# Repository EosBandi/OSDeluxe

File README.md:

# OSDeluxe

OSDeluxe is a color OSD with four video input, Picture in Picture function for Mavlink flight controllers. It using a Renesas TW2837 Video Mux ASIC
and a Teensy 3.2.

# History

This project, just like many others has a long history. It started as blue screen eliminator, for FPV flights. Before custom made FPV monitors, it was a constant problem that normal monitors went dark or blue when video signal become noisy. A cheap video quad switch based on a TW2823 (earlier version of the chip currently used) was reprogrammed to digitize incoming video in a free running mode, and since it already had four inputs and PIP capabilities it was also added to the mix. (The idea come from a Russian webpage http://we.easyelectronics.ru/howwork/kvadrator-izobrazheniya-dlya-sistem-videonablyudeniya.html and confidential datasheet of TW2823 was found on Chinese page.) 
The TW2823 chip has color OSD capabilities and it seemed a good idea to make a PIP OSD for FPV use with it. After experimenting for a while it turned out that the speed of OSD functions are too slow to use  for FPV, so the project was stalled. Then a new version of the chip come out, the TW2837 with accelerated OSD functions. Using these functions with some tuned code, now it is possible to have a decent color OSD with around 10Hz refresh rate.

# TW2837
The TW2837 is a four channel video and audio controller designed for security applications by Renesas (Originally TechWell, then Intersil). It has four PAL/NTSC video decoders (digitizers) and dual video encoders. Video encoders has scalers and video enhancer built in. Decoders and encoders are connected to a MUX engine which provides two display paths and an accelerated graphic overlay (OSD) for each paths. Unlike older TW28xx chips, datasheet for TW2837 is freely available.  (unfortunately OSD sections of the datasheet are quite rudimentary, so it needed a lots of experimenting to make it work.)
Communication with the chip can be done via I2C interface (up to 10Mhz!! clock speed) or via a parallel interface.

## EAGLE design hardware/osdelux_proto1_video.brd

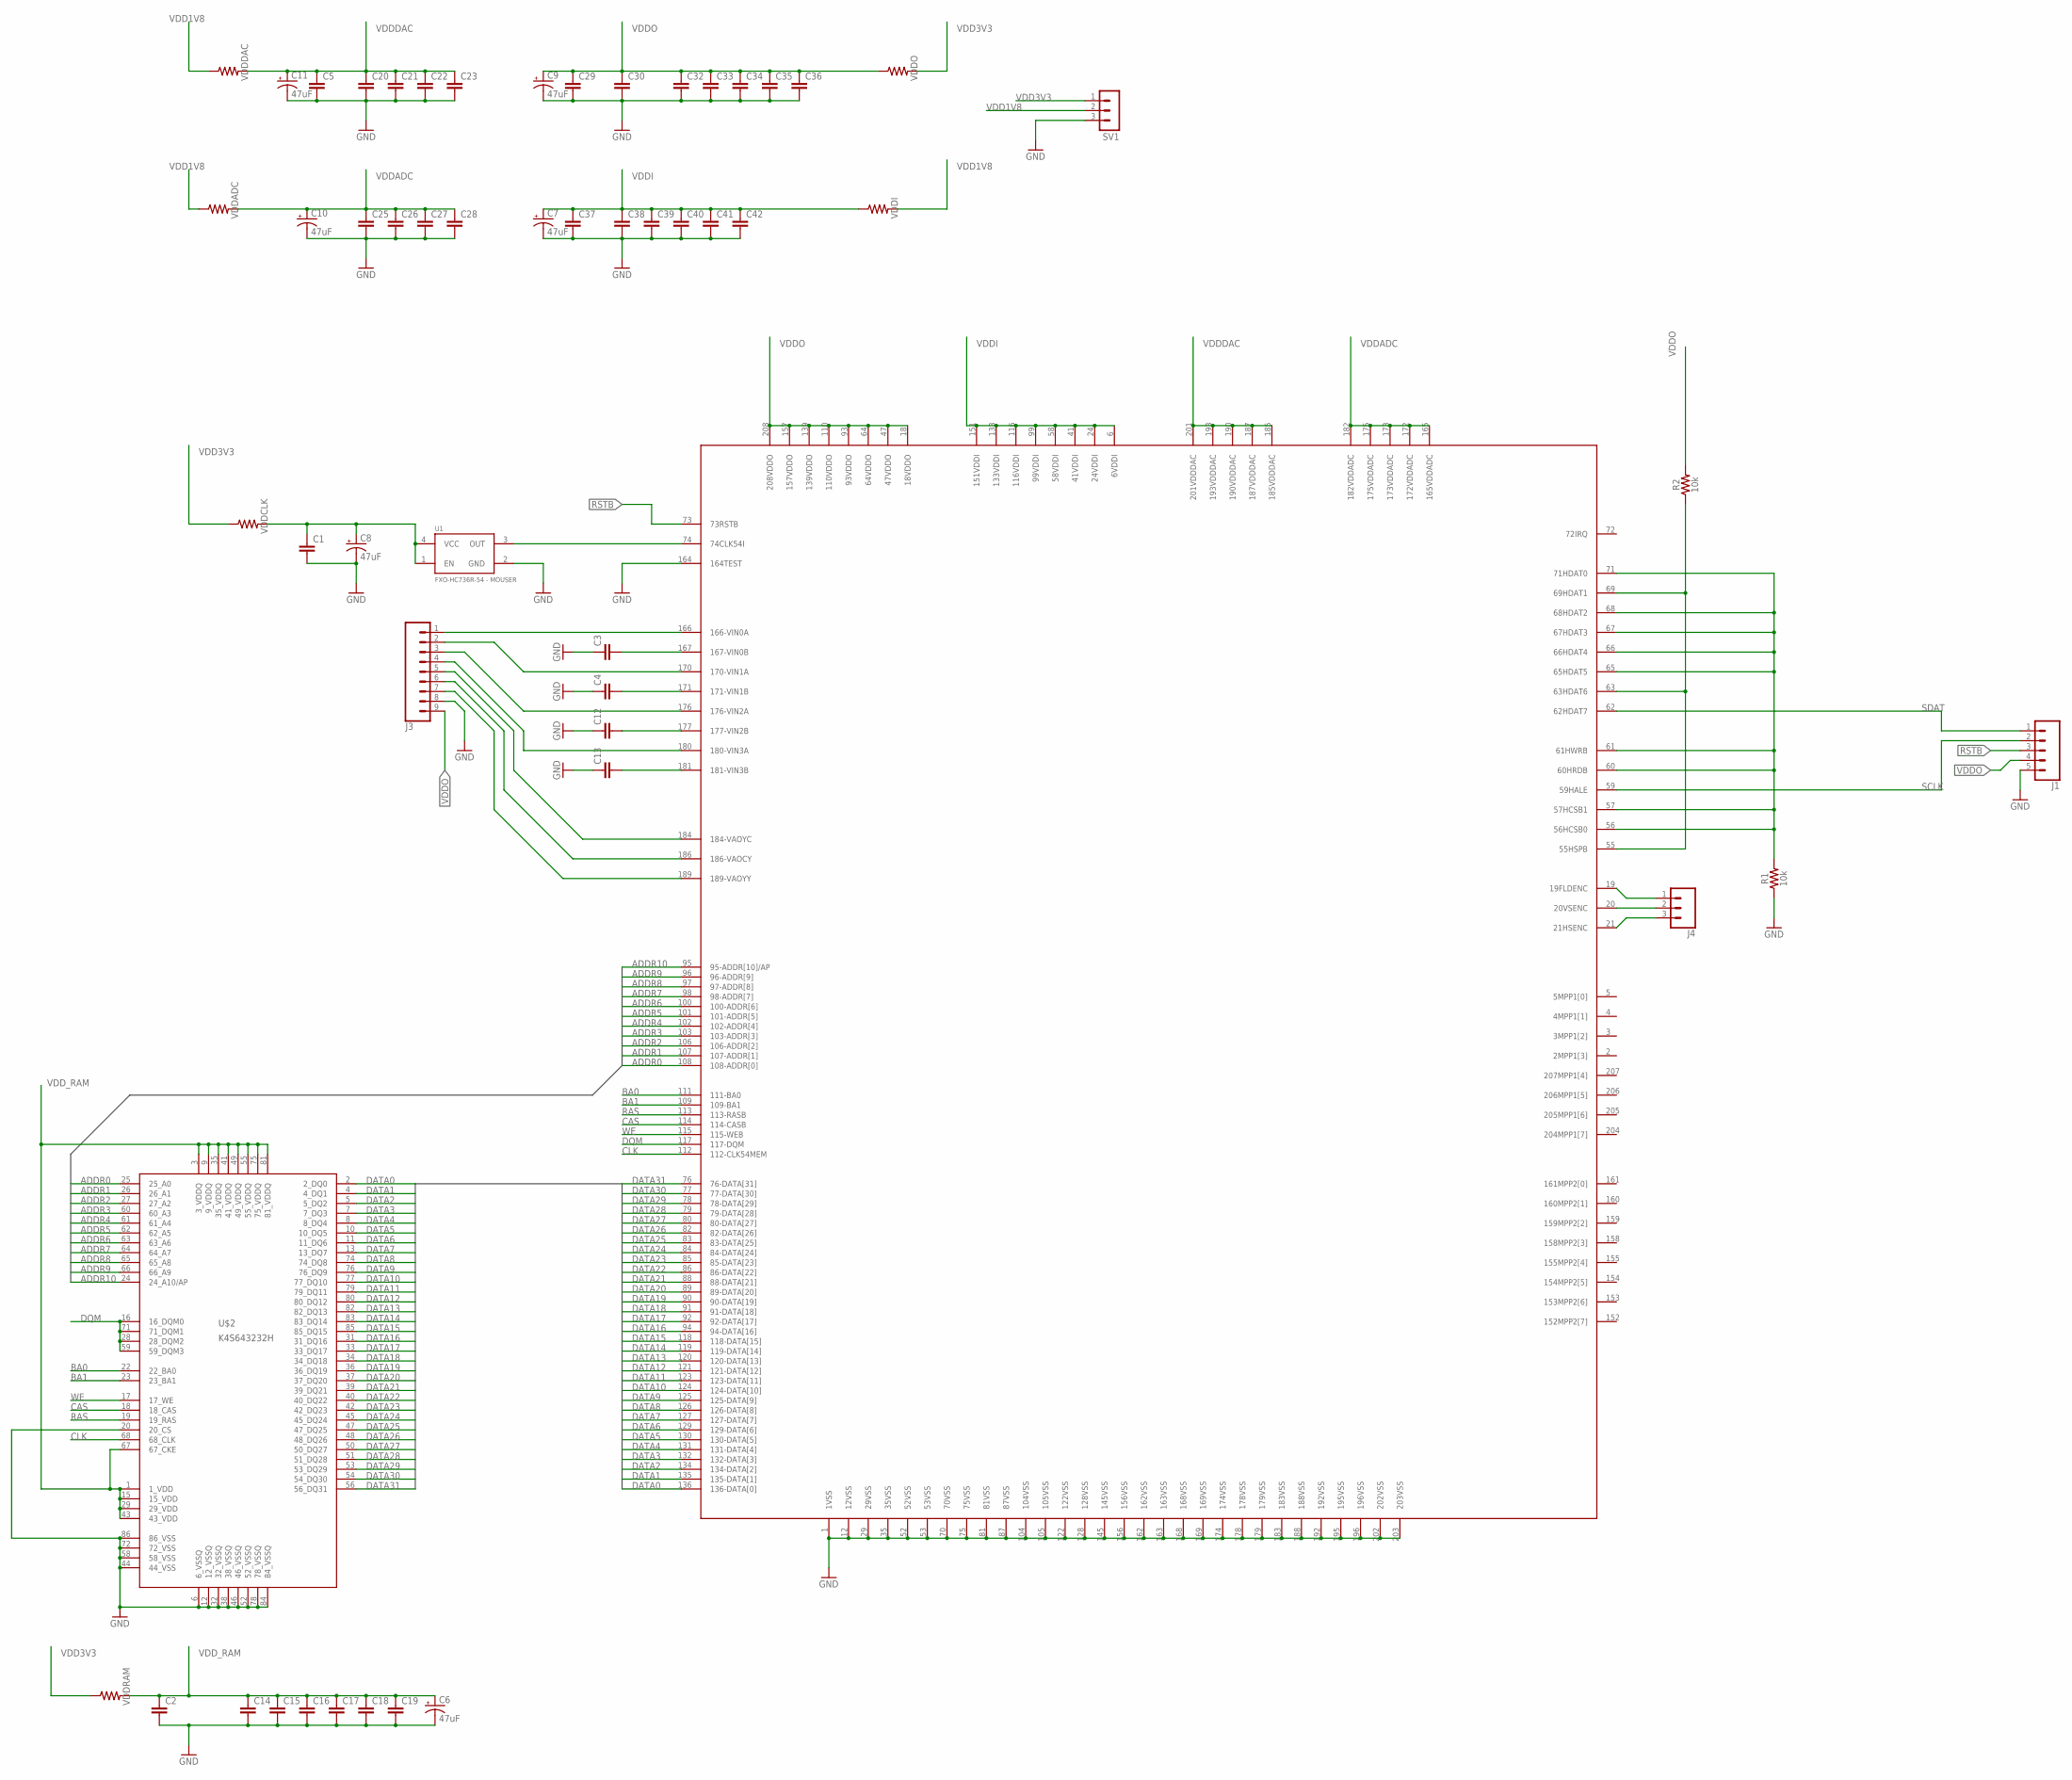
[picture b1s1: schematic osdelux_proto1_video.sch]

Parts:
C1, C2, C3, C4, C5, C12, C13, C14, C15, C16, C17, C18, C19, C20, C21, C22, C23, C25, C26, C27, C28, C29, C30, C32, C33, C34, C35, C36, C37, C38, C39, C40, C41, C42: CAP0805; 0805
C6, C7, C8, C9, C10, C11: 47uF; EIA3528
J1: CONN_05LOCK_LONGPADS; 1X05_LOCK_LONGPADS
J3: CONN_09LOCK-LONGPADS; 1X09_LOCK_LONGPADS
J4: CONN_03LOCK_LONGPADS; 1X03_LOCK_LONGPADS
R1, R2: 10k; 0805
SV1: MA03-1
U1: FXO-HC736R-54 - MOUSER; CRYSTAL-SMD-7.5X5.2-6PIN
U$1: TW2823; LQFP208
U$2: K4S643232H; TSOP86
VDDADC: 1206
VDDCLK: 1206
VDDDAC: 1206
VDDI: 1206
VDDO: 1206
VDDRAM: 1206

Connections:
72IRQ: U$1.72 (72IRQ)
ADDR0: U$1.108 (108-ADDR[0]), U$2.25 (25_A0)
ADDR1: U$1.107 (107-ADDR[1]), U$2.26 (26_A1)
ADDR2: U$1.106 (106-ADDR[2]), U$2.27 (27_A2)
ADDR3: U$1.103 (103-ADDR[3]), U$2.60 (60_A3)
ADDR4: U$1.102 (102-ADDR[4]), U$2.61 (61_A4)
ADDR5: U$1.101 (101-ADDR[5]), U$2.62 (62_A5)
ADDR6: U$1.100 (100-ADDR[6]), U$2.63 (63_A6)
ADDR7: U$1.98 (98-ADDR[7]), U$2.64 (64_A7)
ADDR8: U$1.97 (97-ADDR[8]), U$2.65 (65_A8)
ADDR9: U$1.96 (96-ADDR[9]), U$2.66 (66_A9)
ADDR10: U$1.95 (95-ADDR[10]/AP), U$2.24 (24_A10/AP)
BA0: U$1.111 (111-BA0), U$2.22 (22_BA0)
BA1: U$1.109 (109-BA1), U$2.23 (23_BA1)
CAS: U$1.114 (114-CASB), U$2.18 (18_CAS)
CLK: U$1.112 (112-CLK54MEM), U$2.68 (68_CLK)
DATA0: U$1.136 (136-DATA[0]), U$2.2 (2_DQ0)
DATA1: U$1.135 (135-DATA[1]), U$2.4 (4_DQ1)
DATA2: U$1.134 (134-DATA[2]), U$2.5 (5_DQ2)
DATA3: U$1.132 (132-DATA[3]), U$2.7 (7_DQ3)
DATA4: U$1.131 (131-DATA[4]), U$2.8 (8_DQ4)
DATA5: U$1.130 (130-DATA[5]), U$2.10 (10_DQ5)
DATA6: U$1.129 (129-DATA[6]), U$2.11 (11_DQ6)
DATA7: U$1.127 (127-DATA[7]), U$2.13 (13_DQ7)
DATA8: U$1.126 (126-DATA[8]), U$2.74 (74_DQ8)
DATA9: U$1.125 (125-DATA[9]), U$2.76 (76_DQ9)
DATA10: U$1.124 (124-DATA[10]), U$2.77 (77_DQ10)
DATA11: U$1.123 (123-DATA[11]), U$2.79 (79_DQ11)
DATA12: U$1.121 (121-DATA[12]), U$2.80 (80_DQ12)
DATA13: U$1.120 (120-DATA[13]), U$2.82 (82_DQ13)
DATA14: U$1.119 (119-DATA[14]), U$2.83 (83_DQ14)
DATA15: U$1.118 (118-DATA[15]), U$2.85 (85_DQ15)
DATA16: U$1.94 (94-DATA[16]), U$2.31 (31_DQ16)
DATA17: U$1.92 (92-DATA[17]), U$2.33 (33_DQ17)
DATA18: U$1.91 (91-DATA[18]), U$2.34 (34_DQ18)
DATA19: U$1.90 (90-DATA[19]), U$2.36 (36_DQ19)
DATA20: U$1.89 (89-DATA[20]), U$2.37 (37_DQ20)
DATA21: U$1.88 (88-DATA[21]), U$2.39 (39_DQ21)
DATA22: U$1.86 (86-DATA[22]), U$2.40 (40_DQ22)
DATA23: U$1.85 (85-DATA[23]), U$2.42 (42_DQ23)
DATA24: U$1.84 (84-DATA[24]), U$2.45 (45_DQ24)
DATA25: U$1.83 (83-DATA[25]), U$2.47 (47_DQ25)
DATA26: U$1.82 (82-DATA[26]), U$2.48 (48_DQ26)
DATA27: U$1.80 (80-DATA[27]), U$2.50 (50_DQ27)
DATA28: U$1.79 (79-DATA[28]), U$2.51 (51_DQ28)
DATA29: U$1.78 (78-DATA[29]), U$2.53 (53_DQ29)
DATA30: U$1.77 (77-DATA[30]), U$2.54 (54_DQ30)
DATA31: U$1.76 (76-DATA[31]), U$2.56 (56_DQ31)
DQM: U$1.117 (117-DQM), U$2.16 (16_DQM0), U$2.28 (28_DQM2), U$2.59 (59_DQM3), U$2.71 (71_DQM1)
FLD: J4.1, U$1.19 (19FLDENC)
GND: C1.2, C2.2, C3.1, C4.1, C5.2, C6.C (-), C7.C (-), C8.C (-), C9.C (-), C10.C (-), C11.C (-), C12.1, C13.1, C14.2, C15.2, C16.2, C17.2, C18.2, C19.2, C20.2, C21.2, C22.2, C23.2, C25.2, C26.2, C27.2, C28.2, C29.2, C30.2, C32.2, C33.2, C34.2, C35.2, C36.2, C37.2, C38.2, C39.2, C40.2, C41.2, C42.2, J1.5, J3.8, R1.1, SV1.3, U1.2 (GND), U$1.1 (1VSS), U$1.12 (12VSS), U$1.29 (29VSS), U$1.35 (35VSS), U$1.52 (52VSS), U$1.53 (53VSS), U$1.70 (70VSS), U$1.75 (75VSS), U$1.81 (81VSS), U$1.87 (87VSS), U$1.104 (104VSS), U$1.105 (105VSS), U$1.122 (122VSS), U$1.128 (128VSS), U$1.145 (145VSS), U$1.156 (156VSS), U$1.162 (162VSS), U$1.163 (163VSS), U$1.164 (164TEST), U$1.168 (168VSS), U$1.169 (169VSS), U$1.174 (174VSS), U$1.178 (178VSS), U$1.179 (179VSS), U$1.183 (183VSS), U$1.188 (188VSS), U$1.192 (192VSS), U$1.195 (195VSS), U$1.196 (196VSS), U$1.202 (202VSS), U$1.203 (203VSS), U$2.6 (6_VSSQ), U$2.12 (12_VSSQ), U$2.20 (20_CS), U$2.32 (32_VSSQ), U$2.38 (38_VSSQ), U$2.44 (44_VSS), U$2.46 (46_VSSQ), U$2.52 (52_VSSQ), U$2.58 (58_VSS), U$2.72 (72_VSS), U$2.78 (78_VSSQ), U$2.84 (84_VSSQ), U$2.86 (86_VSS)
HSYNC: J4.3, U$1.21 (21HSENC)
unnamed: C1.1, C8.A (+), U1.1 (EN), U1.4 (VCC), VDDCLK.2
unnamed: U1.3 (OUT), U$1.74 (74CLK54I)
unnamed: C3.2, U$1.167 (167-VIN0B)
unnamed: C4.2, U$1.171 (171-VIN1B)
unnamed: C12.2, U$1.177 (177-VIN2B)
unnamed: C13.2, U$1.181 (181-VIN3B)
unnamed: R1.2, U$1.56 (56HCSB0), U$1.57 (57HCSB1), U$1.60 (60HRDB), U$1.61 (61HWRB), U$1.65 (65HDAT5), U$1.66 (66HDAT4), U$1.67 (67HDAT3), U$1.68 (68HDAT2), U$1.71 (71HDAT0)
unnamed: R2.1, U$1.55 (55HSPB), U$1.63 (63HDAT6), U$1.69 (69HDAT1)
RAS: U$1.113 (113-RASB), U$2.19 (19_RAS)
RSTB: J1.3, U$1.73 (73RSTB)
SCLK: J1.2, U$1.59 (59HALE)
SDAT: J1.1, U$1.62 (62HDAT7)
VAOCY: J3.6, U$1.186 (186-VAOCY)
VAOYC: J3.5, U$1.184 (184-VAOYC)
VAOYY: J3.7, U$1.189 (189-VAOYY)
VDD1V8: SV1.2, VDDADC.1, VDDDAC.1, VDDI.2
VDD3V3: SV1.1, VDDCLK.1, VDDO.2, VDDRAM.1
VDDADC: C10.A (+), C25.1, C26.1, C27.1, C28.1, U$1.165 (165VDDADC), U$1.172 (172VDDADC), U$1.173 (173VDDADC), U$1.175 (175VDDADC), U$1.182 (182VDDADC), VDDADC.2
VDDDAC: C5.1, C11.A (+), C20.1, C21.1, C22.1, C23.1, U$1.185 (185VDDDAC), U$1.187 (187VDDDAC), U$1.190 (190VDDDAC), U$1.193 (193VDDDAC), U$1.201 (201VDDDAC), VDDDAC.2
VDDI: C7.A (+), C37.1, C38.1, C39.1, C40.1, C41.1, C42.1, U$1.6 (6VDDI), U$1.24 (24VDDI), U$1.41 (41VDDI), U$1.58 (58VDDI), U$1.99 (99VDDI), U$1.116 (116VDDI), U$1.133 (133VDDI), U$1.151 (151VDDI), VDDI.1
VDDO: C9.A (+), C29.1, C30.1, C32.1, C33.1, C34.1, C35.1, C36.1, J1.4, J3.9, R2.2, U$1.18 (18VDDO), U$1.47 (47VDDO), U$1.64 (64VDDO), U$1.93 (93VDDO), U$1.110 (110VDDO), U$1.139 (139VDDO), U$1.157 (157VDDO), U$1.208 (208VDDO), VDDO.1
VDD_RAM: C2.1, C6.A (+), C14.1, C15.1, C16.1, C17.1, C18.1, C19.1, U$2.1 (1_VDD), U$2.3 (3_VDDQ), U$2.9 (9_VDDQ), U$2.15 (15_VDD), U$2.29 (29_VDD), U$2.35 (35_VDDQ), U$2.41 (41_VDDQ), U$2.43 (43_VDD), U$2.49 (49_VDDQ), U$2.55 (55_VDDQ), U$2.67 (67_CKE), U$2.75 (75_VDDQ), U$2.81 (81_VDDQ), VDDRAM.2
VIN0: J3.1, U$1.166 (166-VIN0A)
VIN1: J3.2, U$1.170 (170-VIN1A)
VIN2: J3.3, U$1.176 (176-VIN2A)
VIN3: J3.4, U$1.180 (180-VIN3A)
VSYNC: J4.2, U$1.20 (20VSENC)
WE: U$1.115 (115-WEB), U$2.17 (17_WE)

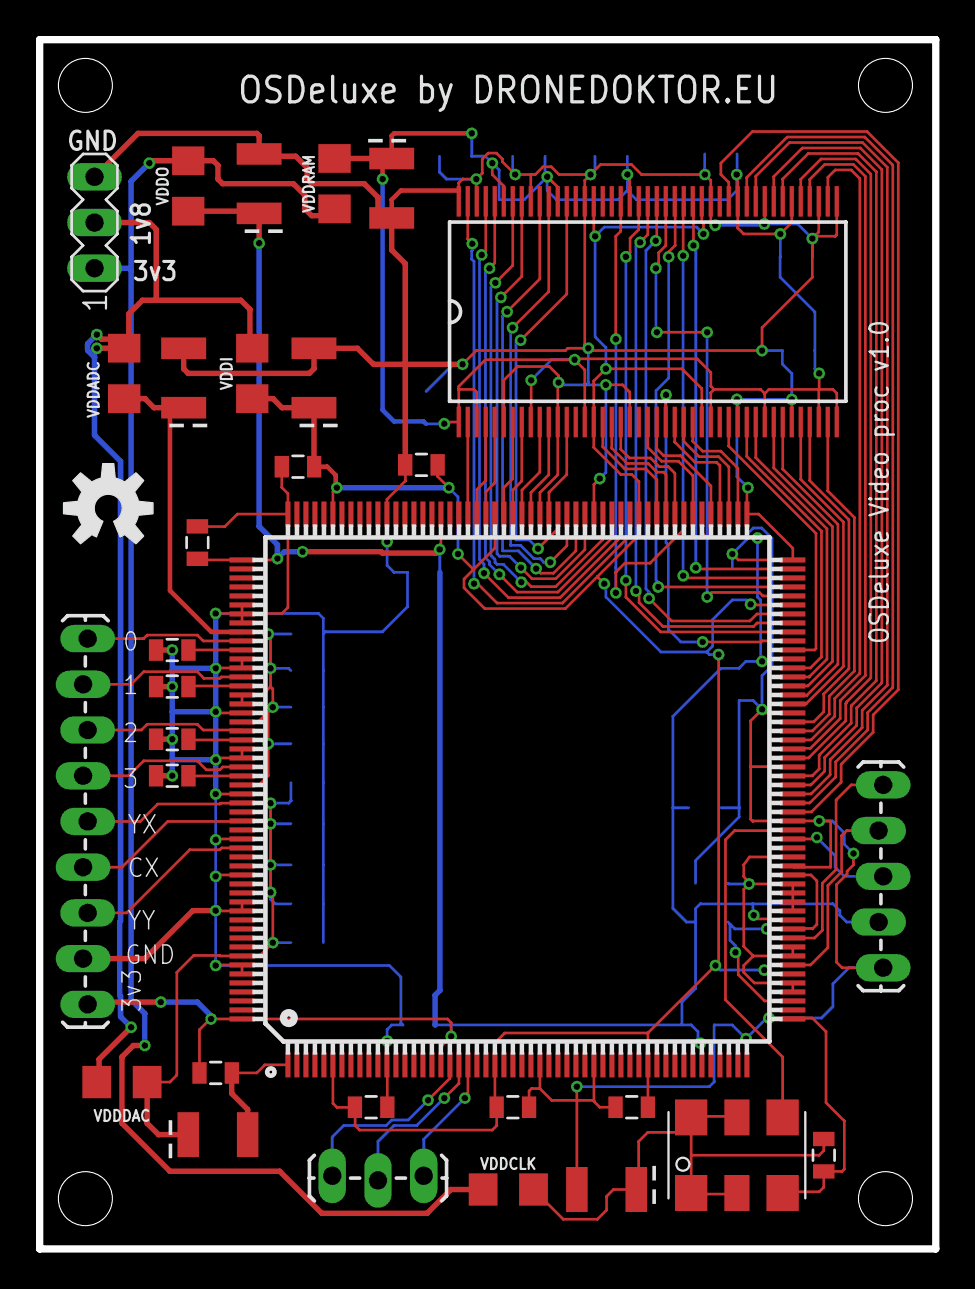
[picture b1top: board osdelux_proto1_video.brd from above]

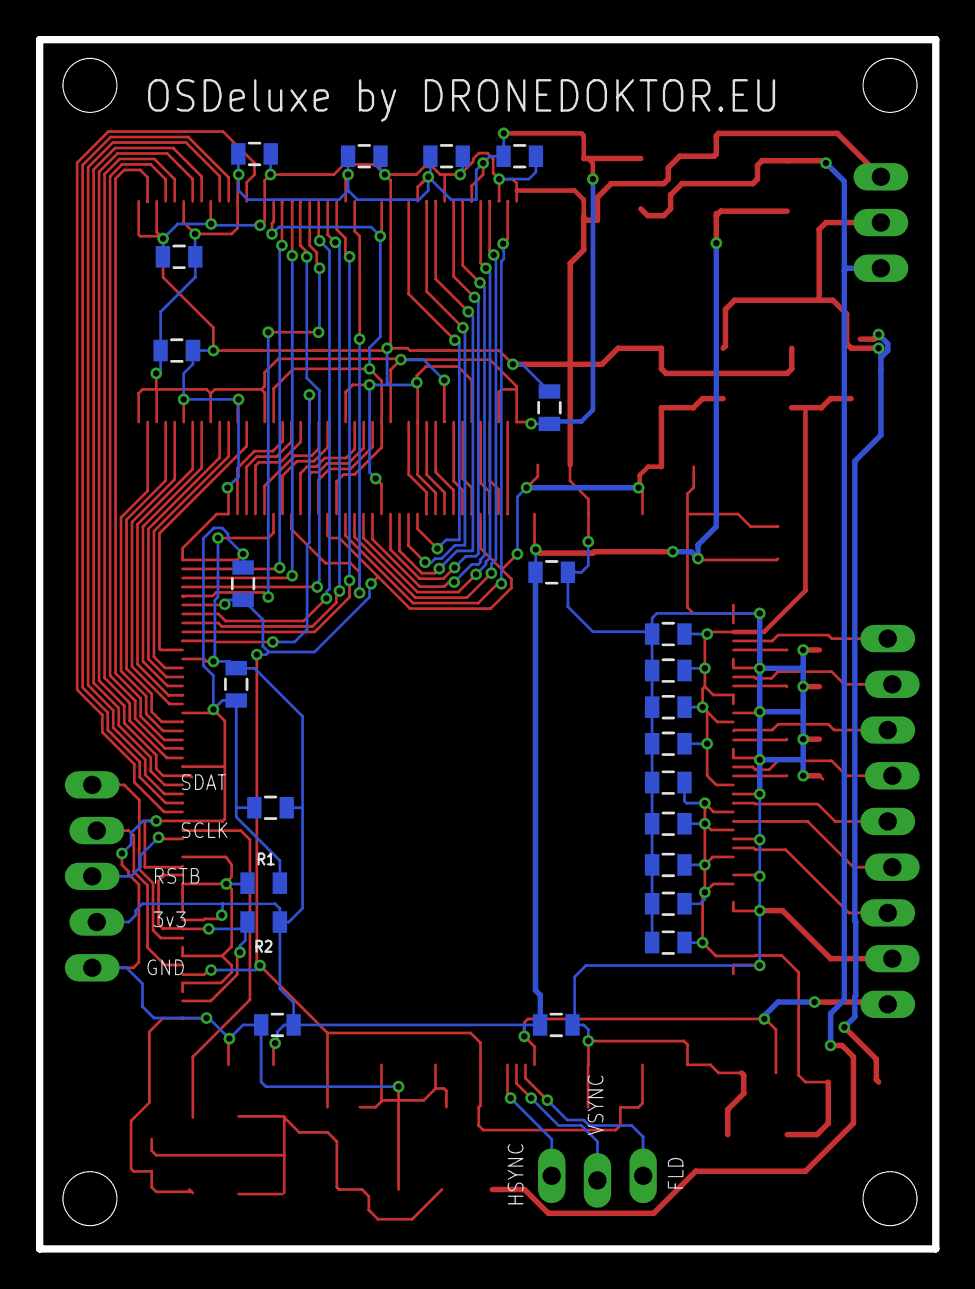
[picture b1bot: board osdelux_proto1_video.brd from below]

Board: 2 copper layers, 49.8 x 67.2 mm, 56 parts (24 on the bottom side), 79 nets.

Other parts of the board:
U$3: OSHW-LOGO-M

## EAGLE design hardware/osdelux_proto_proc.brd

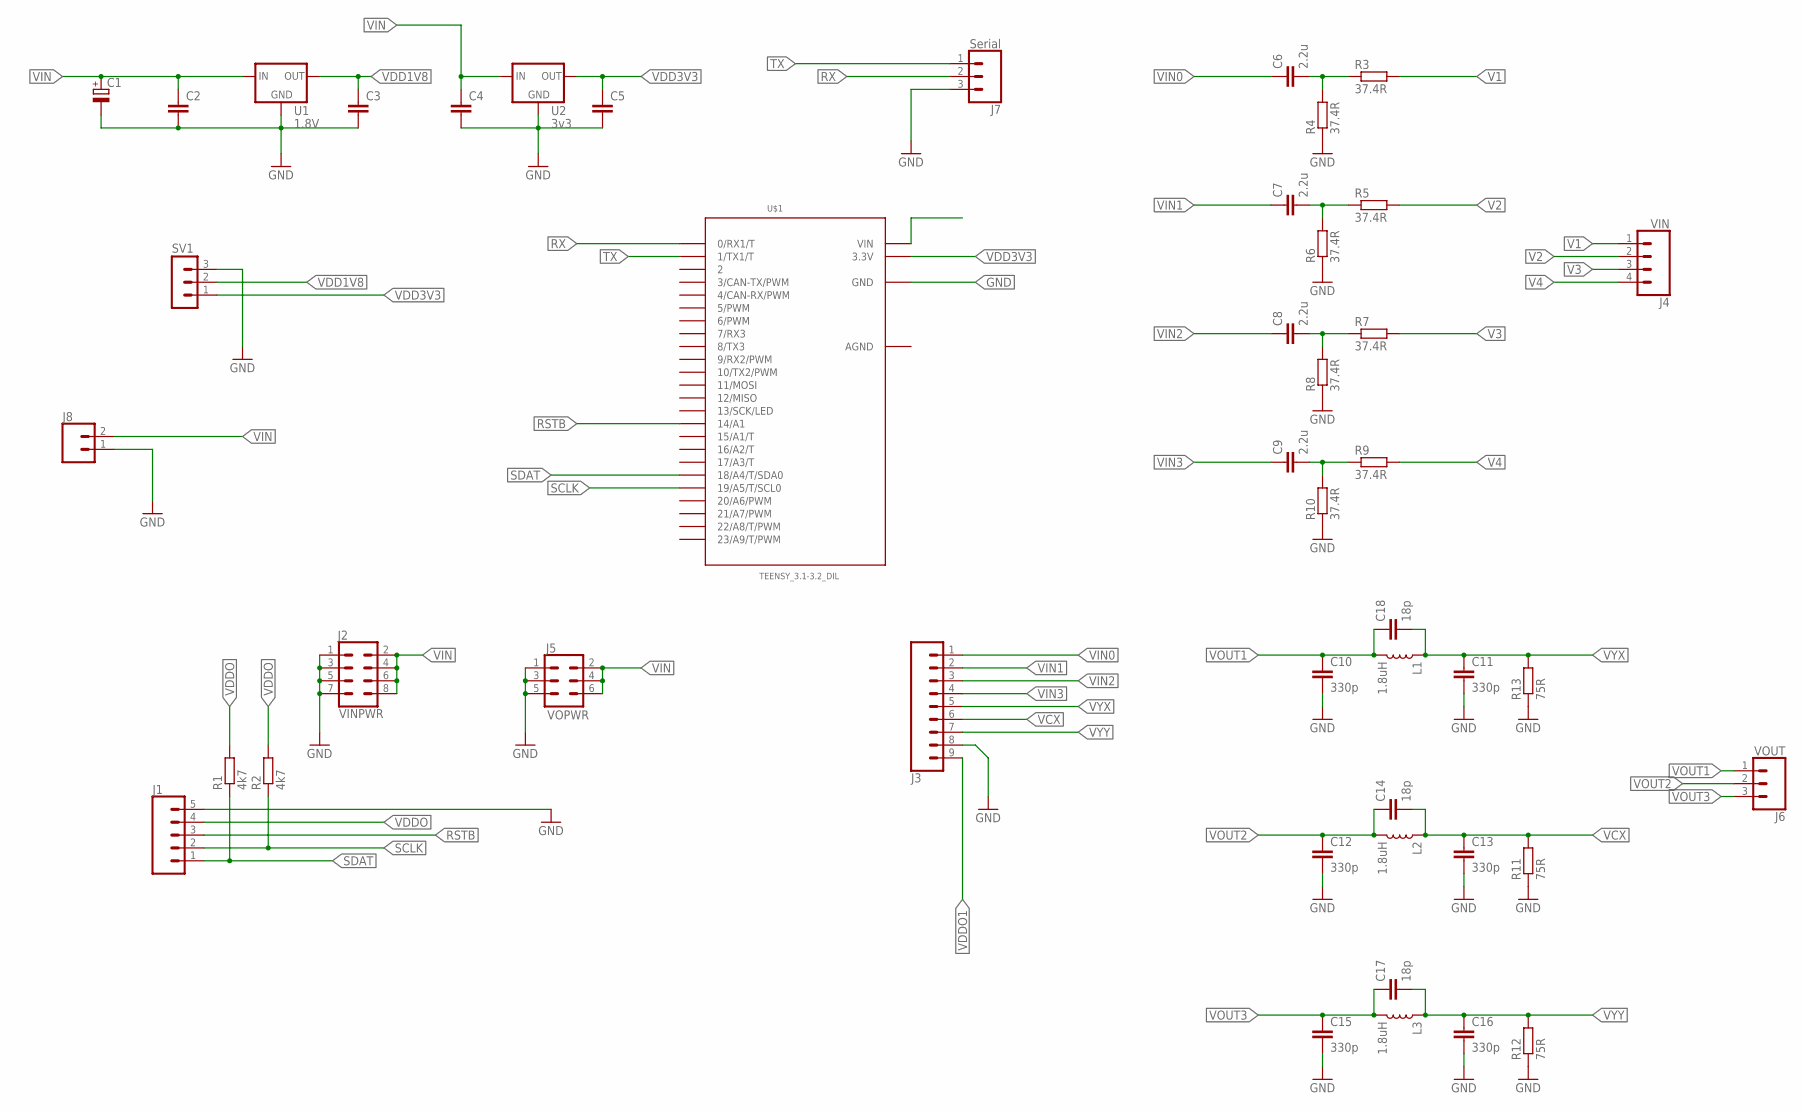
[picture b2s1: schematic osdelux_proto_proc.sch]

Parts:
C1: CPOL-EUE3.5-8; E3,5-8
C2, C3, C4, C5: C-EUC1206K; C1206K
C6, C7, C8, C9: 2.2u; C1206
C10, C11, C12, C13, C15, C16: 330p; C0805
C14, C17, C18: 18p; C0805
J1: CONN_05LOCK_LONGPADS; 1X05_LOCK_LONGPADS
J2: VINPWR; 2X4
J3: CONN_09LOCK-LONGPADS; 1X09_LOCK_LONGPADS
J4: VIN; 1X04
J5: VOPWR; 2X3
J6: VOUT; 1X03
J7: Serial; 1X03
J8: CONN_02LOCK_LONGPADS; 1X02_LOCK_LONGPADS
L1, L2, L3: 1.8uH; 0805
R1, R2: 4k7; R0805
R3, R4, R5, R6, R7, R8, R9, R10: 37.4R; R0805
R11, R12, R13: 75R; R0805
SV1: MA03-1
U1: 1.8V; DC-DC_CONVERTER_78XX
U2: 3v3; DC-DC_CONVERTER_78XX
U$1: TEENSY_3.1-3.2_DIL; TEENSY_3.0-3.2&LC_DIL

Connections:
AGND: U$1.AGND
DCIN: U$1.VIN
GND: C1.-, C2.2, C3.2, C4.2, C5.2, C10.2, C11.2, C12.2, C13.2, C15.2, C16.2, J1.5, J2.1, J2.3, J2.5, J2.7, J3.8, J5.1, J5.3, J5.5, J7.3, J8.1, R4.1, R6.1, R8.1, R10.1, R11.1, R12.1, R13.1, SV1.3, U1.GND, U2.GND, U$1.GND
unnamed: C6.2, R3.1, R4.2
unnamed: C7.2, R5.1, R6.2
unnamed: C8.2, R7.1, R8.2
unnamed: C9.2, R9.1, R10.2
RSTB: J1.3, U$1.14/A0 (14/A1)
RX: J7.2, U$1.0 (0/RX1/T)
SCLK: J1.2, R2.1, U$1.19/A5 (19/A5/T/SCL0)
SDAT: J1.1, R1.1, U$1.18/A4 (18/A4/T/SDA0)
TX: J7.1, U$1.1 (1/TX1/T)
V1: J4.1, R3.2
V2: J4.2, R5.2
V3: J4.3, R7.2
V4: J4.4, R9.2
VCX: C13.1, C14.2, J3.6, L2.1, R11.2
VDD1V8: C3.1, SV1.2, U1.VOUT (OUT)
VDD3V3: C5.1, SV1.1, U2.VOUT (OUT), U$1.3.3V
VDDO: J1.4, R1.2, R2.2
VDDO1: J3.9
VIN: C1.+, C2.1, C4.1, J2.2, J2.4, J2.6, J2.8, J5.2, J5.4, J5.6, J8.2, U1.VIN (IN), U2.VIN (IN)
VIN0: C6.1, J3.1
VIN1: C7.1, J3.2
VIN2: C8.1, J3.3
VIN3: C9.1, J3.4
VOUT1: C10.1, C18.1, J6.1, L1.2
VOUT2: C12.1, C14.1, J6.2, L2.2
VOUT3: C15.1, C17.1, J6.3, L3.2
VYX: C11.1, C18.2, J3.5, L1.1, R13.2
VYY: C16.1, C17.2, J3.7, L3.1, R12.2

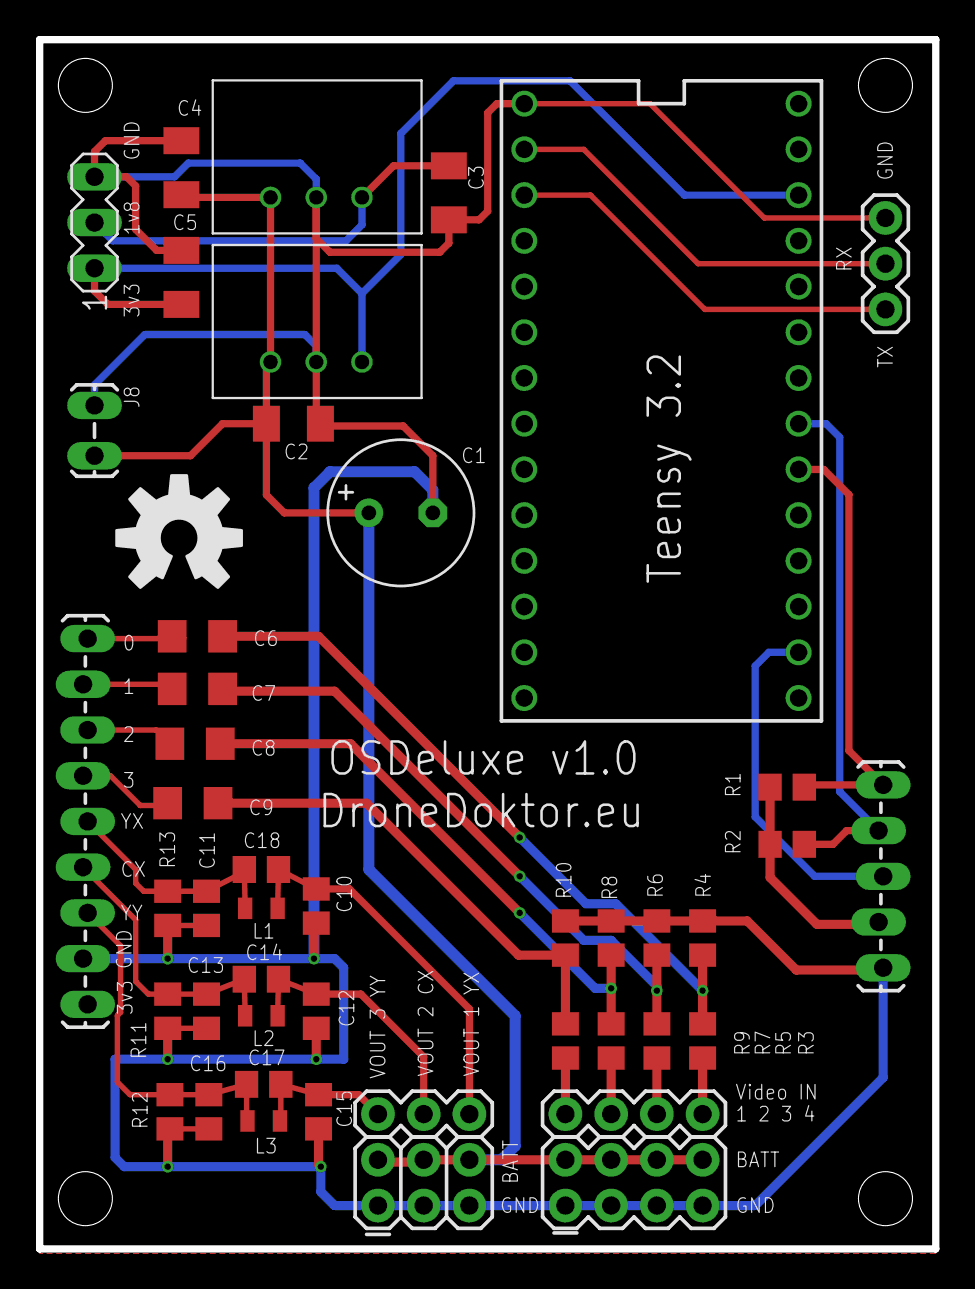
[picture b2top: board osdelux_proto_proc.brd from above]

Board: 2 copper layers, 49.8 x 67.2 mm, 47 parts (0 on the bottom side), 28 nets.

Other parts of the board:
U$2: OSHW-LOGO-L

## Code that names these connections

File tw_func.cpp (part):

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    tw_write_register(0x105, 0b00000100); // bypass mode when video loss is detected

    // Input selection for each scaler in the display path
    tw_write_register(0x080, 0x00); // ch0 scaler - VIN0 pin
    tw_write_register(0x090, 0x40); // ch1 scaler - VIN1 pin
    tw_write_register(0x0a0, 0x80); // ch2 scaler - VIN2 pin
    tw_write_register(0x0b0, 0xc0); // ch3 scaler - VIN3 pin

    // Channel mode selection
    tw_write_register(0x110, 0x00); // channel 0 disable, no popup   bit7-enable, bit6-popup, bit1-0 As see below
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
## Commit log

2018-01-21 Add mavlink submodule
2018-01-24 Refactor font handling, added outline font., added mavlink stuff
2018-01-25 added some widgets (work in progress)
2018-01-27 Update bar widget
2018-01-27 widgets are ready
2018-01-28 settings
2018-01-28 added mavlink initial processing
2018-01-29 Mavlink
2018-01-29 more mavlink
2018-01-29 small changes
2018-01-29 failsafe blink fix
2018-01-30 small fixes
2018-01-31 mavlink, home, messages on REC osd
2018-01-31 small color change in message
2018-02-03 ekf, current, armed
2018-02-03 battery capacity request from controller
2018-02-03 First release
2018-02-03 change home position
2018-02-03 Added license informations
2018-02-11 Moved development to VS2017 and Visual Micro
2018-02-11 VS1027 solution files
2018-03-03 Added weight cell data display
2018-03-03 Sort out rc controls
2018-03-03 RC control fixes
2018-03-03 Batt capacity query reinstate
2018-03-03 cell count to 12
2018-03-03 default values fix
2018-03-11 Restructure TW init section and change to TW2837
2018-03-12 work in progress
2018-03-16 interim
2018-03-17 Added PARAMS handling
2018-03-19 Refactor widgets and add vido parameters
2018-03-31 aaaaa
2018-03-31 Added video pip parameters
2018-04-01 Added a lot of things
2018-04-01 Added message_achive but it is too slow for constant rendering, must be moved to rec or need scratch buffer font display....
2018-04-02 Reworked vin settings
2018-04-02 Test hires osd
2018-04-05 Added OSD256 font handling
2018-04-06 Finished (mostly the OSD256 font stuff) changed horizon to high res
2018-04-06 Added circle draw
2018-04-07 Manyu changes, speed up drawing. And finished horizon and gps widget. Prepared bitmaps for status widget
2018-04-08 bitmap handling, bar drawing and battery, alt widgets rewrite for OSD256 done
2018-04-08 converting to osd256 commencted out old osd functions
2018-04-08 Cleaned up tw_* functions
2018-04-08 Center marker added Ground speed added
2018-04-09 movement indicator
2018-04-09 font table init
2018-04-10 Bar behind data line at he bottom. Quick fix for GigaCopter6. Will move to a optional settings later.
2018-04-12 move global variables out from osd. struct into g. no need to save them
2018-04-12 Code cleanup, eliminate almost all compiler warnings
2018-04-13 Seeting save via mavlink params More cleanup
2018-04-16 Code cleanup Compass widget Vario graph widget Speedup OSD256_block_fill
2018-04-16 Added quick horizon
2018-04-16 Some more speed enhancements
2018-04-17 Battery cell autodetect Radar first implementation
2018-04-17 Added wp to radar Auto mode display distance to next waypoint
2018-04-17 Clean up U8 and U16 references Integrated radar widget
2018-08-11 Some fixes
2018-08-12 Add rssi moved string to strings.h Do some code cleanup for clean compile
2018-08-12 Clean up
2018-08-12 Change from U8 and U16 to uint8_t and utin16_t
2018-08-12 Refactoring OSD256 functions
2018-08-12 Remove empty files
2018-08-12 Some more renaming and refactoring
2018-08-12 Remove todo and coderep
2018-08-12 Added hw design files
2018-08-12 Added TW2837 datasheet
2018-08-12 Added some comments
2018-08-12 Correct typo
2018-08-12 Some cleanup in parameters
2018-08-12 preparing for release to the public
2018-08-13 readme
2018-08-13 rfeadme
2018-08-20 Added paralell interface for TW2837
2018-08-20 Some cleanup
2018-09-18 Added _vm to the .gitignore file
2018-09-18 Directory cleanup
2018-09-18 More directory cleanup
2019-08-24 Moved to v3 hardware and add some new widgets
2019-08-25 Added vibe bars
2019-08-25 add parameters for ekf and vibe bargraph
2019-08-25 Updates and cleanup
2019-08-25 add rcout widget

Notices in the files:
tw_func.cpp:
Copyright (C) 2018  Andras Schaffer - Dronedoktor.eu
This program is free software: you can redistribute it and/or modify
it under the terms of the GNU General Public License as published by
the Free Software Foundation, either version 3 of the License, or
(at your option) any later version.
parts and their libraries:
SparkFun-Resistors: Licensing: Creative Commons ShareAlike 4.0 International - https://creativecommons.org/licenses/by-sa/4.0
